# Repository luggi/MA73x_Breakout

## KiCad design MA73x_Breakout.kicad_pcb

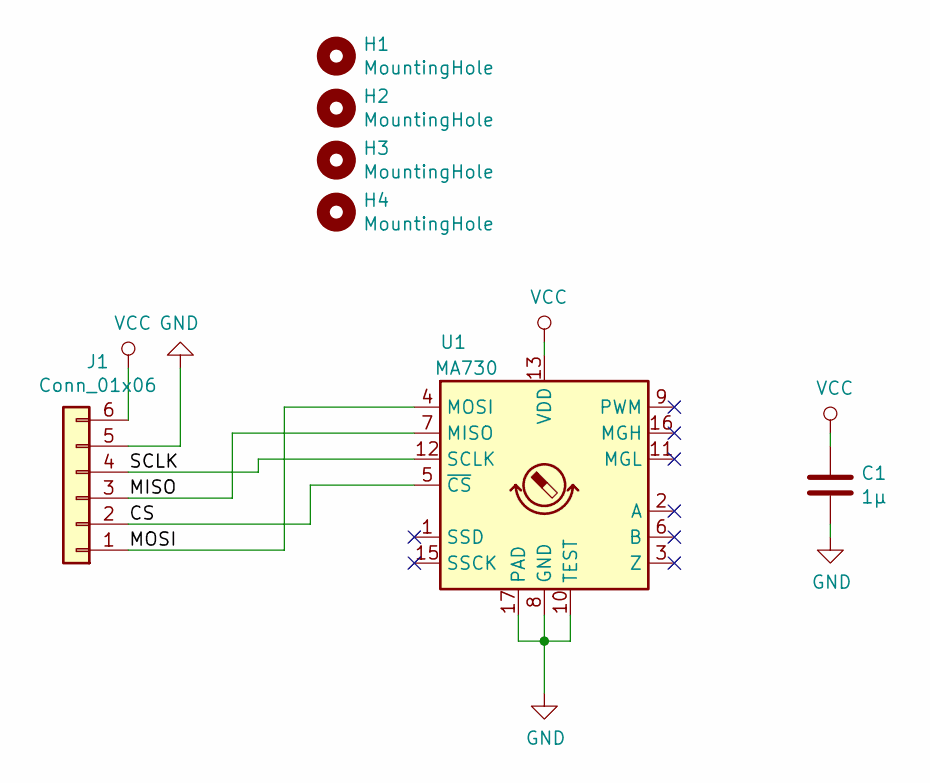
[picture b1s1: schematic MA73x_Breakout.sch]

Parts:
C1: 1µ; C_0603_1608Metric_Pad1.05x0.95mm_HandSolder
H1, H2, H3, H4: MountingHole; MountingHole_3.2mm_M3
J1: Conn_01x06; JST_SH_BM06B-SRSS-TB_1x06-1MP_P1.00mm_Vertical
U1: MA730; QFN-16-1EP_3x3mm_P0.5mm_EP1.75x1.75mm

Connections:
/CS: J1.2, U1.5 (~CS)
/MISO: J1.3, U1.7 (MISO)
/MOSI: J1.1, U1.4 (MOSI)
/SCLK: J1.4, U1.12 (SCLK)
GND: C1.2, J1.5, U1.8 (GND), U1.10 (TEST), U1.17 (PAD)
VCC: C1.1, J1.6, U1.13 (VDD)

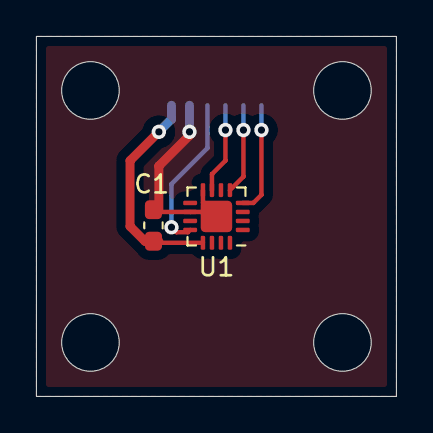
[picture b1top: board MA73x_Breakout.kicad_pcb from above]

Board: 2 copper layers, 20.0 x 20.0 mm, 7 parts (1 on the bottom side), 6 nets.

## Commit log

2020-11-09 rev_0.1
